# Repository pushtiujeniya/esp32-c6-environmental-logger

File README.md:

# ESP32-C6 Environmental Sensor Station & Data Logger

An open-source, 4-layer IoT environmental monitoring station and telemetry data logger powered by the **ESP32-C6-WROOM-1** microcontroller. This board utilizes multi-protocol wireless connectivity (Wi-Fi 6, BLE 5, and Zigbee/Thread) to read atmospheric and gas sensors, display local telemetry, and securely back up data to a local MicroSD card.

---

## 🛠 Core Features & Hardware

### 1. Processor & Wireless Connectivity
* **MCU:** ESP32-C6-WROOM-1
* **Programming/Debugging:** On-board dual-purpose interfaces for flashing and debugging via a protected USB-C 2.0 interface.
* 
### 2. Comprehensive Sensor Array
* **SCD41-D-R2:** Photoacoustic $CO_2$ sensor measuring true carbon dioxide levels in ppm ($I^2C$ Address: `0x62`).
* **SGP41-D-R4:** Digital gas sensor providing multi-pixel MOx sensing for VOC (Volatile Organic Compounds) and $NO_x$ (Nitrogen Oxides) indoor environmental indexes ($I^2C$ Address: `0x59`).
* **HDC2033:** Low-power, high-accuracy digital temperature and relative humidity sensor ($I^2C$ Address: `0x44`).

### 3. Storage & User Interface
* **MicroSD Card Slot:** Dedicated SPI-driven logging interface with individual inline trace damping resistors and pull-ups for secure local data logging.
* **OLED Display (SSD1306):** 0.96" $I^2C$ graphic display panel for live visual terminal outputs and local troubleshooting ($I^2C$ Address: `0x3C`).

### 4. Power & Battery Management
* **Charging:** TP4056 lithium battery management IC with automated charge/discharging  indicator LEDs.
* **Power Path Switching:** Automated hardware power routing utilizing an AO3401A P-Channel MOSFET to seamlessly switch between USB power and Battery power.
* **Regulator:** AP2112K-3.3V Ultra-low dropout, low-noise LDO regulator supplying clean $3.3\text{V}$ power rails up to $600\text{mA}$ to the wireless MCU and sensors.

### 5. Push Button Switch
* **Reset switch** A button with ESD protection  to reset the MCU 
* **BOOT switch** A BOOT switch button to enter into bootloading mode for new firmware flashing
  
### 5. I2C and UART Pin Connector
* External i2c pin header
* External UART pin header  

---

## 🎛 4-Layer PCB Stackup Architecture

This board is structured with an optimized 4-layer stackup:

* **Layer 1 (Top Copper - F.Cu):** High-speed digital signals, data busses ($I^2C$, SPI), and  component placement.
* **Layer 2 (Internal Plane 1 - In1.Cu):** Solid Ground Plane (GND) providing direct, uninterrupted return paths for low EMI noise and optimal RF shielding.
* **Layer 3 (Internal Plane 2 - In2.Cu):** Split Power Plane ($+5\text{V}$, $+3.3\text{V}$, $\text{VBAT}$) providing low-impedance power distribution directly below signal lines.
* **Layer 4 (Bottom Copper - B.Cu):** Secondary signal traces and clean copper pours for thermal dissipation.

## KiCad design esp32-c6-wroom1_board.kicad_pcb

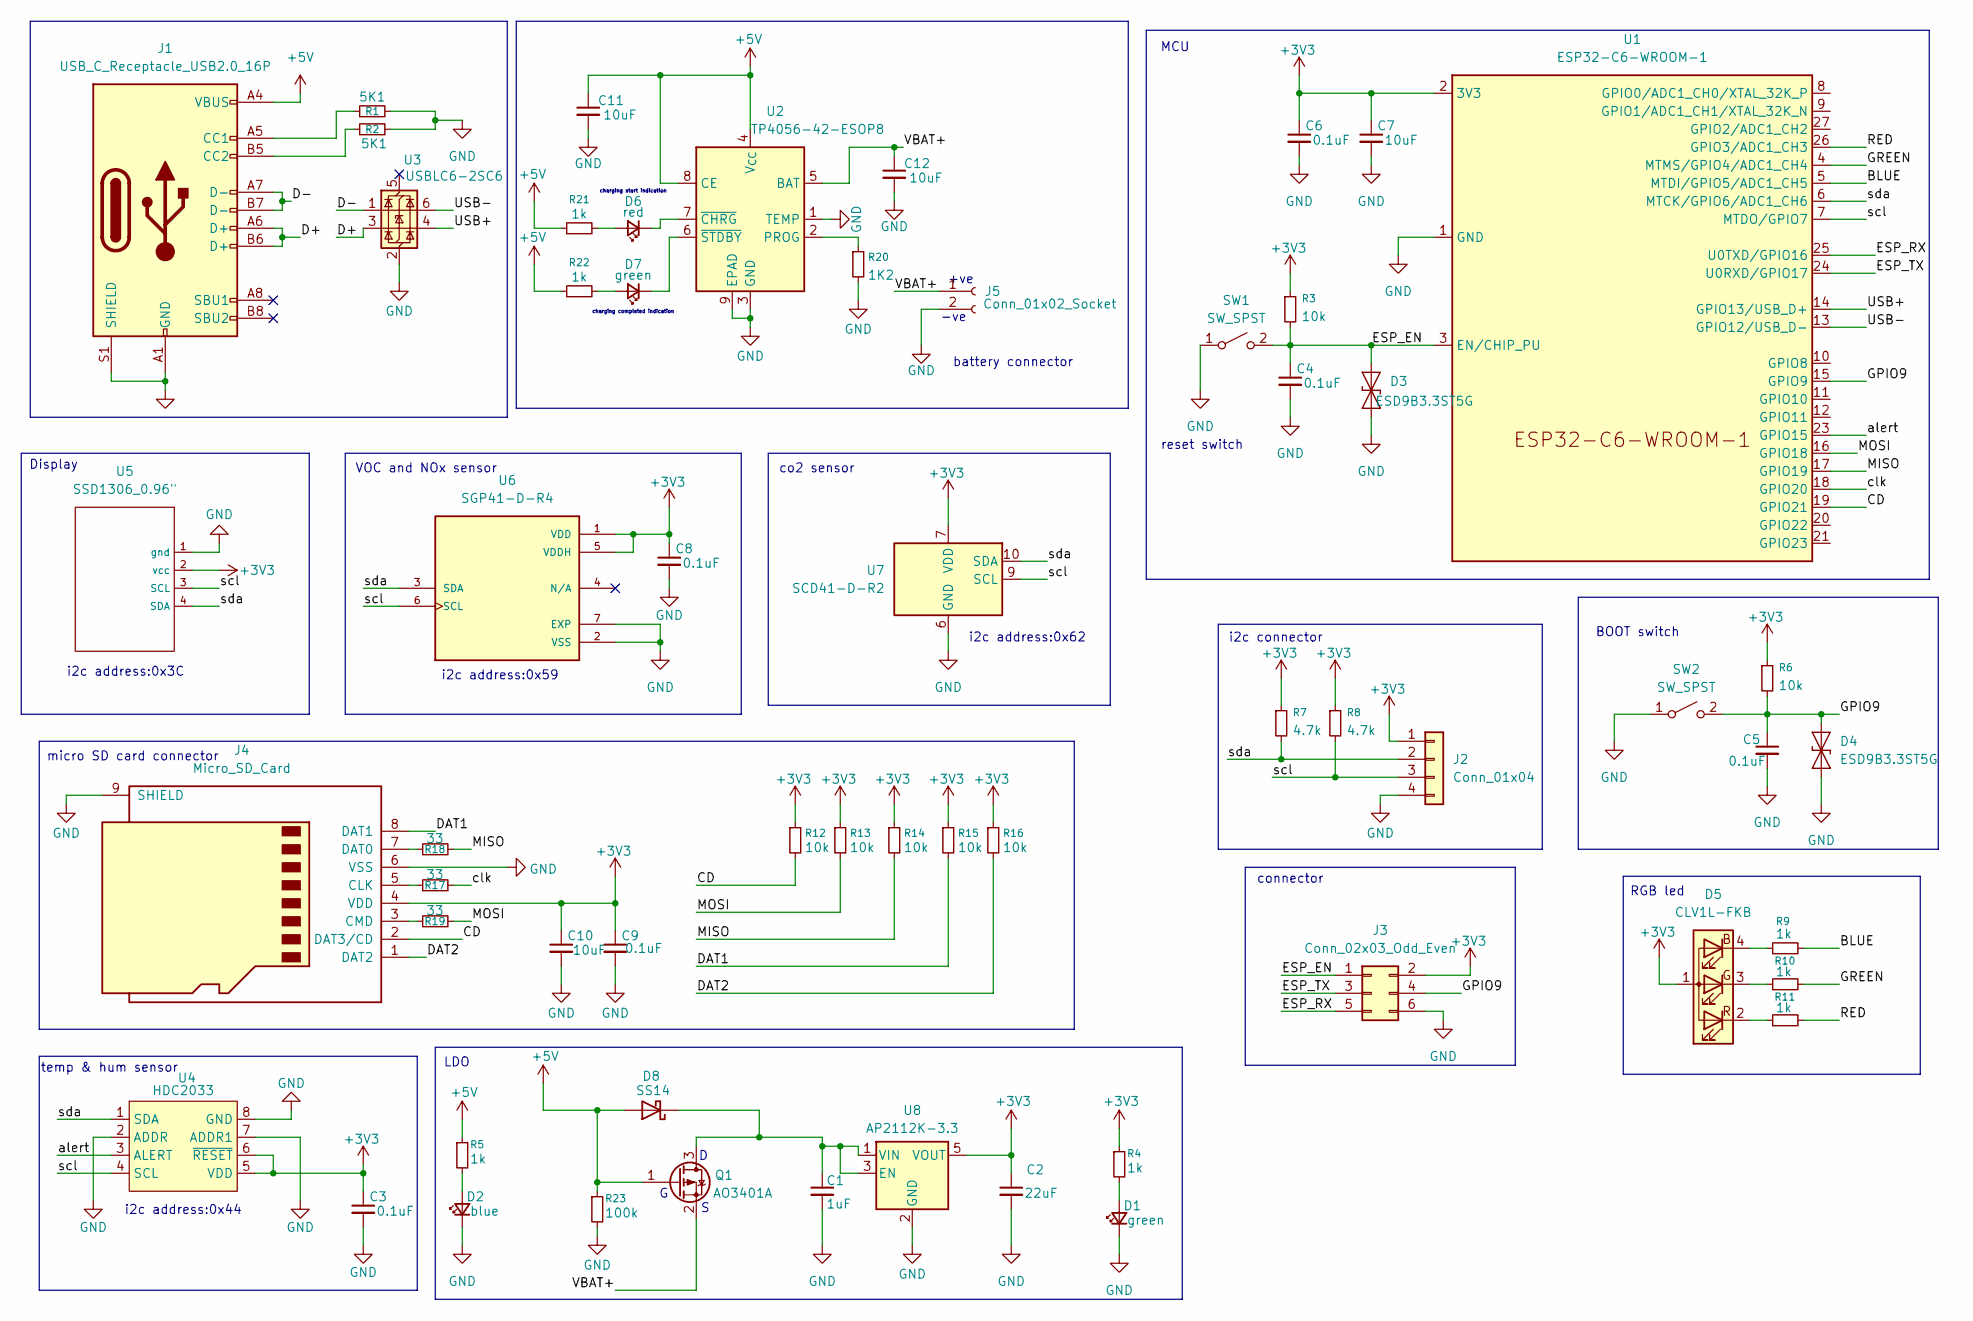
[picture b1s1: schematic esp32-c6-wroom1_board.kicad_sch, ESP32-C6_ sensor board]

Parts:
C1: 1uF; C_0603_1608Metric
C2: 22uF; CP_EIA-1608-08_AVX-J
C3, C4, C5, C6: 0.1uF; C_0603_1608Metric
C7, C10, C11, C12: 10uF; CP_EIA-1608-08_AVX-J
C8: 0.1uF; CP_EIA-1608-08_AVX-J
C9: 0.1uF; R_0805_2012Metric
D1, D7: green; LED_0603_1608Metric_Pad1.05x0.95mm_HandSolder
D2: blue; LED_0603_1608Metric_Pad1.05x0.95mm_HandSolder
D3, D4: ESD9B3.3ST5G; D_SOD-923
D5: CLV1L-FKB; LED_Cree-PLCC4_3.2x2.8mm_CCW
D6: red; LED_0603_1608Metric_Pad1.05x0.95mm_HandSolder
D8: SS14; D_SMA
J1: USB_C_Receptacle_USB2.0_16P; USB_C_Receptacle_XKB_U262-16XN-4BVC11
J2: Conn_01x04; PinHeader_1x04_P2.54mm_Vertical
J3: Conn_02x03_Odd_Even; PinHeader_2x03_P2.54mm_Vertical
J4: Micro_SD_Card; microSD_HC_Molex_104031-0811
J5: Conn_01x02_Socket; JST_XH_B2B-XH-A_1x02_P2.50mm_Vertical
Q1: AO3401A; SOT-23
R1, R2: 5K1; R_0805_2012Metric
R3, R6, R12, R13, R14, R15, R16: 10k; R_0805_2012Metric
R4, R5, R9, R10, R11, R21, R22: 1k; R_0805_2012Metric
R7, R8: 4.7k; R_0805_2012Metric
R17, R18, R19: 33; R_0805_2012Metric
R20: 1K2; R_0805_2012Metric
R23: 100k; R_0805_2012Metric
SW1, SW2: SW_SPST; SW_PUSH_6mm_H8mm
U1: ESP32-C6-WROOM-1
U2: TP4056-42-ESOP8; SOIC-8-1EP_3.9x4.9mm_P1.27mm_EP2.41x3.3mm_ThermalVias
U3: USBLC6-2SC6; SOT-23-6
U4: HDC2033; WSON-8-1EP_2x2mm_P0.5mm_EP0.9x1.6mm
U5: SSD1306_0.96"; 128x64OLED
U6: SGP41-D-R4; XDCR_SGP41-D-R4; PARTREV 1.0
U7: SCD41-D-R2; Sensirion_SCD4x-1EP_10.1x10.1mm_P1.25mm_EP4.8x4.8mm
U8: AP2112K-3.3; SOT-23-5

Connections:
+3V3: C2.1, C3.1, C6.1, C7.1, C8.1, C9.1, C10.1, D5.1 (A), J2.1, J3.2, J4.4 (VDD), R3.1, R4.1, R6.1, R7.1, R8.1, R12.1, R13.1, R14.1, R15.1, R16.1, U1.2 (3V3), U4.5 (VDD), U4.6 (~RESET), U5.2 (vcc), U6.1 (VDD), U6.5 (VDDH), U7.7 (VDD), U7.19 (VDD), U8.5 (VOUT)
+5V: C11.1, D8.2 (A), J1.A4 (VBUS), J1.A9 (VBUS), J1.B4 (VBUS), J1.B9 (VBUS), Q1.1 (G), R5.1, R21.1, R22.1, R23.1, U2.4 (V_{CC}), U2.8 (CE)
/BLUE: R9.2, U1.5 (MTDI/GPIO5/ADC1_CH5)
/CD: J4.2 (DAT3/CD), R12.2, U1.19 (GPIO21)
/D+: J1.A6 (D+), J1.B6 (D+), U3.3 (I/O2)
/D-: J1.A7 (D-), J1.B7 (D-), U3.1 (I/O1)
/DAT1: J4.8 (DAT1), R15.2
/DAT2: J4.1 (DAT2), R16.2
/ESP_EN: C4.1, D3.2 (A2), J3.1, R3.2, SW1.2 (B), U1.3 (EN/CHIP_PU)
/ESP_RX: J3.5, U1.25 (U0TXD/GPIO16)
/ESP_TX: J3.3, U1.24 (U0RXD/GPIO17)
/GPIO9: C5.1, D4.2 (A2), J3.4, R6.2, SW2.2 (B), U1.15 (GPIO9)
/GREEN: R10.2, U1.4 (MTMS/GPIO4/ADC1_CH4)
/MISO: R14.2, R18.2, U1.17 (GPIO19)
/MOSI: R13.2, R19.2, U1.16 (GPIO18)
/RED: R11.2, U1.26 (GPIO3/ADC1_CH3)
/USB+: U1.14 (GPIO13/USB_D+), U3.4 (I/O2)
/USB-: U1.13 (GPIO12/USB_D-), U3.6 (I/O1)
/VBAT+: C12.1, J5.1, Q1.2 (S), U2.5 (BAT)
/alert: U1.23 (GPIO15), U4.3 (ALERT)
/clk: R17.2, U1.18 (GPIO20)
/scl: J2.3, R8.2, U1.7 (MTDO/GPIO7), U4.4 (SCL), U5.3 (SCL), U6.6 (SCL), U7.9 (SCL)
/sda: J2.2, R7.2, U1.6 (MTCK/GPIO6/ADC1_CH6), U4.1 (SDA), U5.4 (SDA), U6.3 (SDA), U7.10 (SDA)
GND: C1.2, C2.2, C3.2, C4.2, C5.2, C6.2, C7.2, C8.2, C9.2, C10.2, C11.2, C12.2, D1.1 (K), D2.1 (K), D3.1 (A1), D4.1 (A1), J1.A1 (GND), J1.A12 (GND), J1.B1 (GND), J1.B12 (GND), J1.S1 (SHIELD), J2.4, J3.6, J4.6 (VSS), J4.9 (SHIELD), J5.2, R1.2, R2.2, R20.2, R23.2, SW1.1 (A), SW2.1 (A), U1.1 (GND), U1.28 (GND), U1.29 (GND), U2.1 (TEMP), U2.3 (GND), U2.9 (EPAD), U3.2 (GND), U4.2 (ADDR), U4.7 (ADDR1), U4.8 (GND), U5.1 (gnd), U6.2 (VSS), U6.7 (EXP), U7.6 (GND), U7.20 (GND), U7.21 (GND), U8.2 (GND)
unnamed: D1.2 (A), R4.2
unnamed: D2.2 (A), R5.2
unnamed: D5.4 (BK), R9.1
unnamed: D5.3 (GK), R10.1
unnamed: D5.2 (RK), R11.1
unnamed: D6.2 (A), R21.2
unnamed: D6.1 (K), U2.7 (~CHRG)
unnamed: D7.2 (A), R22.2
unnamed: D7.1 (K), U2.6 (~STDBY)
unnamed: C1.1, D8.1 (K), Q1.3 (D), U8.1 (VIN), U8.3 (EN)
unnamed: J1.A5 (CC1), R1.1
unnamed: J1.B5 (CC2), R2.1
unnamed: J4.5 (CLK), R17.1
unnamed: J4.3 (CMD), R19.1
unnamed: J4.7 (DAT0), R18.1
unnamed: R20.1, U2.2 (PROG)

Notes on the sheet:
+ve
temp & hum sensor
i2c connector
micro SD card connector
charging completed indication
BOOT switch
VOC and NOx sensor
RGB led
Display
connector
LDO
i2c address:0x3C
charging start indication
reset switch
battery connector
i2c address:0x62
co2 sensor
MCU
i2c address:0x44
-ve
i2c address:0x59

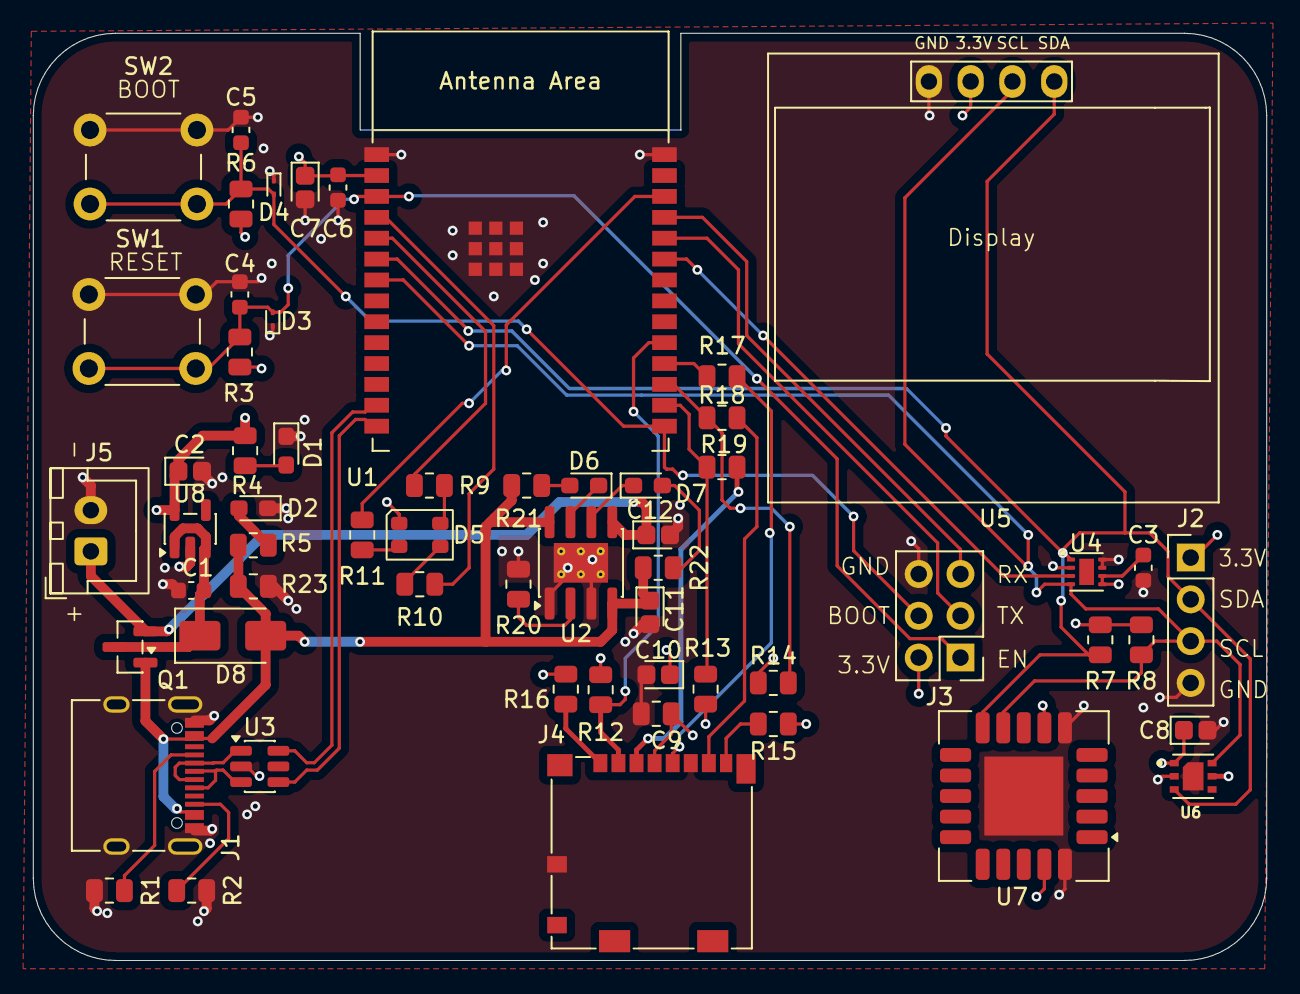
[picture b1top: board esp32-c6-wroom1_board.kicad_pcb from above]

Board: 4 copper layers, 75.0 x 56.4 mm, 59 parts (0 on the bottom side), 40 nets.

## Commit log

2026-06-21 Enhance README with detailed project specifications
    Expanded the README to include detailed features, hardware specifications, and PCB architecture for the ESP32-C6 Environmental Sensor Station.
2026-06-21 Add temporary file to 3D view directory
2026-06-21 3d view images added
2026-06-21 schematic pdf added
2026-06-21 layout pdf added
2026-06-21 project files added
2026-06-21 Add new temp file to external library
2026-06-21 Update README with new hardware features
    Added sections for Push Button Switch and I2C/UART Pin Connector.
2026-06-21 external library added
2026-06-21 Add temporary file to layout images
2026-06-21 All 4 layer layout images added
